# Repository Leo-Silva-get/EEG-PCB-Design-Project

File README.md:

# DIY 8-Channel EEG Acquisition System

### Custom ADS1299 + ESP32-S3 Hardware for Brain-Computer Interface Research

A custom four-layer, eight-channel EEG acquisition PCB designed in KiCad to explore neural signal acquisition and motor-imagery-based brain-computer interfaces.

## Project Overview

This project focuses on designing EEG acquisition hardware from the component level, rather than relying on a commercial EEG development board.

The system is designed around the Texas Instruments ADS1299 analog front end and an ESP32-S3 microcontroller.

**Hardware features:**
- Eight EEG acquisition channels using the ADS1299
- ESP32-S3 microcontroller with SPI communication
- Custom positive and negative analog power supplies
- Electrode input filtering and protection
- USB-C connectivity
- microSD hardware interface for future data recording
- LIS3DH accelerometer for movement measurements
- Four-layer PCB with dedicated internal ground planes

## Engineering Work

Designed the schematic and PCB in KiCad, including component selection, power distribution, signal routing, input filtering, decoupling, and manufacturing documentation.

The project includes Gerber files, an assembly BOM, component placement information, and design source files.

## Current Status

**PCB design completed; professional fabrication and assembly review in progress.**

Hardware bring-up, firmware development, signal characterization, and motor-imagery experiments are planned next.

This design has not yet been validated through physical testing or evaluated for human electrical safety.

## Research Objectives

1. Validate ADS1299 communication and register configuration.
2. Acquire and analyze low-noise EEG signals.
3. Implement real-time sampling and data streaming.
4. Develop signal-processing and classification methods for motor imagery.
5. Explore EEG-based control of computer applications.

## Tools and Technologies

KiCad, ADS1299, ESP32-S3, SPI, analog circuit design, PCB layout, embedded systems, and digital signal processing.

## Safety

This is an experimental research prototype, not a certified medical device. Human-connected use requires appropriate electrical-safety evaluation, including isolation and electrode fault-current assessment.

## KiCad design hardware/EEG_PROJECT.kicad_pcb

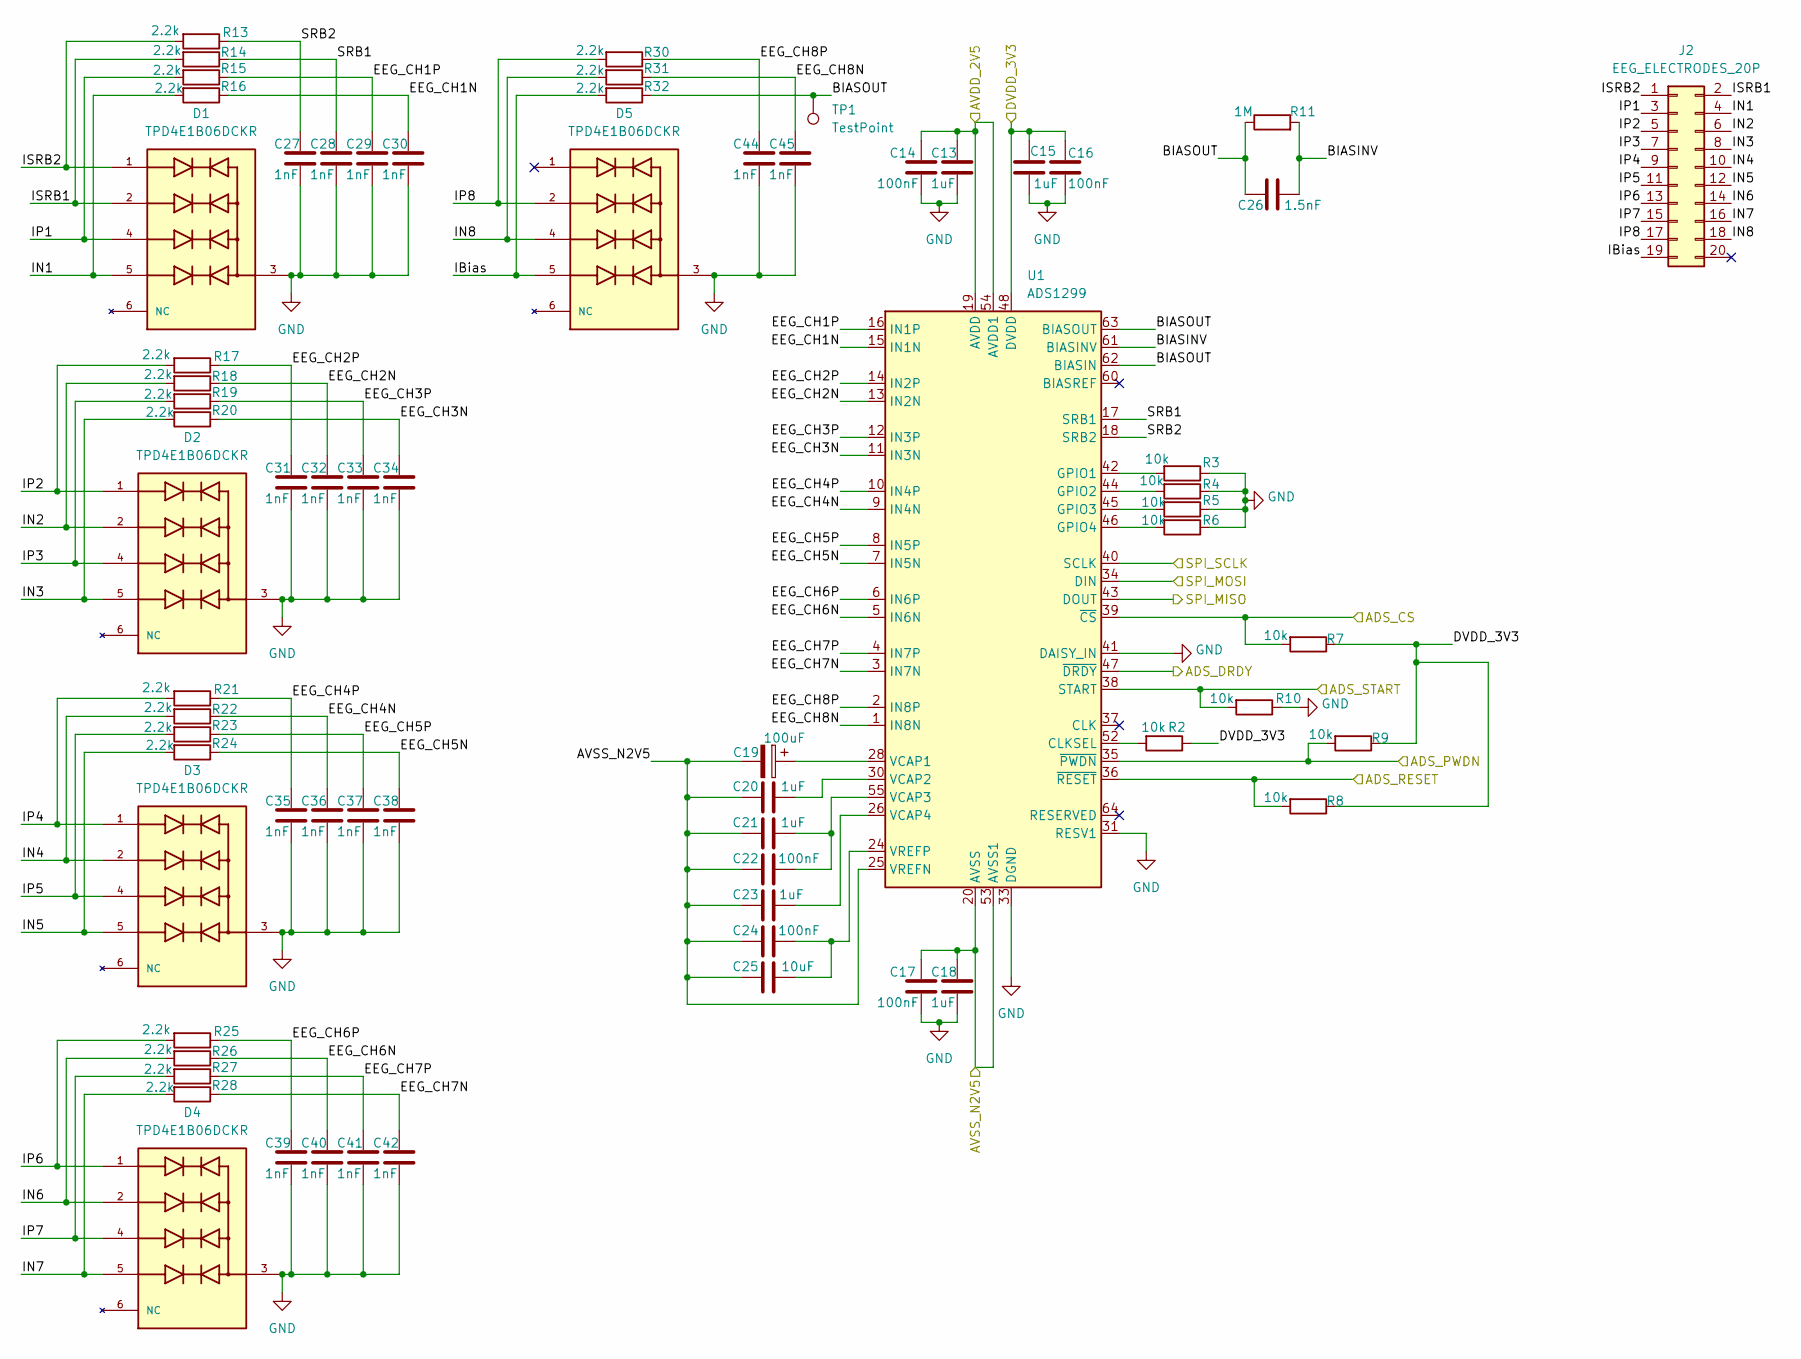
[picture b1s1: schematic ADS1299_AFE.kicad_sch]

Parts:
C13, C15, C18, C20, C21, C23: 1uF; C_0603_1608Metric; Tolerance 10%; Voltage rating 16V; MPN C0603C105K4RACTU
C14, C16, C17, C22, C24: 100nF; C_0603_1608Metric; Tolerance 10%; Voltage rating 100V; MPN GRM188R72A104KA35D
C19: 100uF; CP_EIA-3528-21_Kemet-B; Tolerance 20%; Voltage rating 10V; MPN T495B107M010ATE350
C25: 10uF; C_1206_3216Metric; Tolerance 10%; Voltage rating 16V; MPN GRM31CR71C106KAC7L
C26: 1.5nF; C_0603_1608Metric; Tolerance 5%; Voltage rating 50V; MPN GRM1885C1H152JA01D
C27, C28, C29, C30, C31, C32, C33, C34, C35, C36, C37, C38, C39, C40, C41, C42, C44, C45: 1nF; C_0603_1608Metric; Tolerance 5%; Voltage rating 50V; MPN GRM1885C1H102JA01D
D1, D2, D3, D4, D5: TPD4E1B06DCKR; TVS_TPD4E1B06DCKR; PARTREV C
J2: EEG_ELECTRODES_20P; PinHeader_2x10_P2.54mm_Vertical; MPN TSW-110-07-G-D
R2, R3, R4, R5, R6, R7, R8, R9, R10: 10k; R_0603_1608Metric; Power Rating 0.1 W; Tolerance ±1%; MPN RC0603FR-0710KL
R11: 1M; R_0603_1608Metric; Power Rating 0.1 W; Tolerance ±1%; MPN RC0603FR-071ML
R13, R14, R15, R16, R17, R18, R19, R20, R21, R22, R23, R24, R25, R26, R27, R28, R30, R31, R32: 2.2k; R_0603_1608Metric; Power Rating 0.1 W; Tolerance ±1%; MPN RC0603FR-072K2L
TP1: TestPoint; TestPoint_Pad_D1.5mm; MPN N/A
U1: ADS1299; TQFP-64_10x10mm_P0.5mm; MPN ADS1299IPAG

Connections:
/ADS1299_AFE/ADS_CS: R7.2, U1.39 (~CS); also elsewhere on the board
/ADS1299_AFE/ADS_DRDY: U1.47 (~DRDY); also elsewhere on the board
/ADS1299_AFE/ADS_PWDN: R9.2, U1.35 (~PWDN); also elsewhere on the board
/ADS1299_AFE/ADS_RESET: R8.2, U1.36 (~RESET); also elsewhere on the board
/ADS1299_AFE/ADS_START: R10.2, U1.38 (START); also elsewhere on the board
/ADS1299_AFE/AVDD_2V5: C13.1, C14.1, U1.19 (AVDD), U1.21 (AVDD), U1.22 (AVDD), U1.54 (AVDD1), U1.56 (AVDD), U1.59 (AVDD); also elsewhere on the board
/ADS1299_AFE/AVSS_N2V5: C17.1, C18.1, C19.2, C20.1, C21.1, C22.1, C23.1, C24.1, C25.1, U1.20 (AVSS), U1.23 (AVSS), U1.25 (VREFN), U1.32 (AVSS), U1.53 (AVSS1), U1.57 (AVSS), U1.58 (AVSS); also elsewhere on the board
/ADS1299_AFE/BIASINV: C26.2, R11.2, U1.61 (BIASINV)
/ADS1299_AFE/BIASOUT: C26.1, R11.1, R32.1, TP1.1 (1_1), U1.62 (BIASIN), U1.63 (BIASOUT)
/ADS1299_AFE/DVDD_3V3: C15.1, C16.1, R2.1, R7.1, R8.1, R9.1, U1.48 (DVDD), U1.50 (DVDD); also elsewhere on the board
/ADS1299_AFE/EEG_CH1N: C30.1, R16.1, U1.15 (IN1N)
/ADS1299_AFE/EEG_CH1P: C29.1, R15.1, U1.16 (IN1P)
/ADS1299_AFE/EEG_CH2N: C32.1, R18.1, U1.13 (IN2N)
/ADS1299_AFE/EEG_CH2P: C31.1, R17.1, U1.14 (IN2P)
/ADS1299_AFE/EEG_CH3N: C34.1, R20.1, U1.11 (IN3N)
/ADS1299_AFE/EEG_CH3P: C33.1, R19.1, U1.12 (IN3P)
/ADS1299_AFE/EEG_CH4N: C36.1, R22.1, U1.9 (IN4N)
/ADS1299_AFE/EEG_CH4P: C35.1, R21.1, U1.10 (IN4P)
/ADS1299_AFE/EEG_CH5N: C38.1, R24.1, U1.7 (IN5N)
/ADS1299_AFE/EEG_CH5P: C37.1, R23.1, U1.8 (IN5P)
/ADS1299_AFE/EEG_CH6N: C40.1, R26.1, U1.5 (IN6N)
/ADS1299_AFE/EEG_CH6P: C39.1, R25.1, U1.6 (IN6P)
/ADS1299_AFE/EEG_CH7N: C42.1, R28.1, U1.3 (IN7N)
/ADS1299_AFE/EEG_CH7P: C41.1, R27.1, U1.4 (IN7P)
/ADS1299_AFE/EEG_CH8N: C45.1, R31.1, U1.1 (IN8N)
/ADS1299_AFE/EEG_CH8P: C44.1, R30.1, U1.2 (IN8P)
/ADS1299_AFE/IBias: D5.5, J2.19, R32.2
/ADS1299_AFE/IN1: D1.5, J2.4, R16.2
/ADS1299_AFE/IN2: D2.2, J2.6, R18.2
/ADS1299_AFE/IN3: D2.5, J2.8, R20.2
/ADS1299_AFE/IN4: D3.2, J2.10, R22.2
/ADS1299_AFE/IN5: D3.5, J2.12, R24.2
/ADS1299_AFE/IN6: D4.2, J2.14, R26.2
/ADS1299_AFE/IN7: D4.5, J2.16, R28.2
/ADS1299_AFE/IN8: D5.4, J2.18, R31.2
/ADS1299_AFE/IP1: D1.4, J2.3, R15.2
/ADS1299_AFE/IP2: D2.1, J2.5, R17.2
/ADS1299_AFE/IP3: D2.4, J2.7, R19.2
/ADS1299_AFE/IP4: D3.1, J2.9, R21.2
/ADS1299_AFE/IP5: D3.4, J2.11, R23.2
/ADS1299_AFE/IP6: D4.1, J2.13, R25.2
/ADS1299_AFE/IP7: D4.4, J2.15, R27.2
/ADS1299_AFE/IP8: D5.2, J2.17, R30.2
/ADS1299_AFE/ISRB1: D1.2, J2.2, R14.2
/ADS1299_AFE/ISRB2: D1.1, J2.1, R13.2
/ADS1299_AFE/SPI_MISO: U1.43 (DOUT); also elsewhere on the board
/ADS1299_AFE/SPI_MOSI: U1.34 (DIN); also elsewhere on the board
/ADS1299_AFE/SPI_SCLK: U1.40 (SCLK); also elsewhere on the board
/ADS1299_AFE/SRB1: C28.1, R14.1, U1.17 (SRB1)
/ADS1299_AFE/SRB2: C27.1, R13.1, U1.18 (SRB2)
GND: C13.2, C14.2, C15.2, C16.2, C17.2, C18.2, C27.2, C28.2, C29.2, C30.2, C31.2, C32.2, C33.2, C34.2, C35.2, C36.2, C37.2, C38.2, C39.2, C40.2, C41.2, C42.2, C44.2, C45.2, D1.3, D2.3, D3.3, D4.3, D5.3, R3.1, R4.1, R5.1, R6.1, R10.1, U1.31 (RESV1), U1.33 (DGND), U1.41 (DAISY_IN), U1.49 (DGND), U1.51 (DGND); also elsewhere on the board
unnamed: R2.2, U1.52 (CLKSEL)
unnamed: R3.2, U1.42 (GPIO1)
unnamed: R4.2, U1.44 (GPIO2)
unnamed: R5.2, U1.45 (GPIO3)
unnamed: R6.2, U1.46 (GPIO4)
unnamed: C19.1, U1.28 (VCAP1)
unnamed: C20.2, U1.30 (VCAP2)
unnamed: C21.2, C22.2, U1.55 (VCAP3)
unnamed: C23.2, U1.26 (VCAP4)
unnamed: C24.2, C25.2, U1.24 (VREFP)

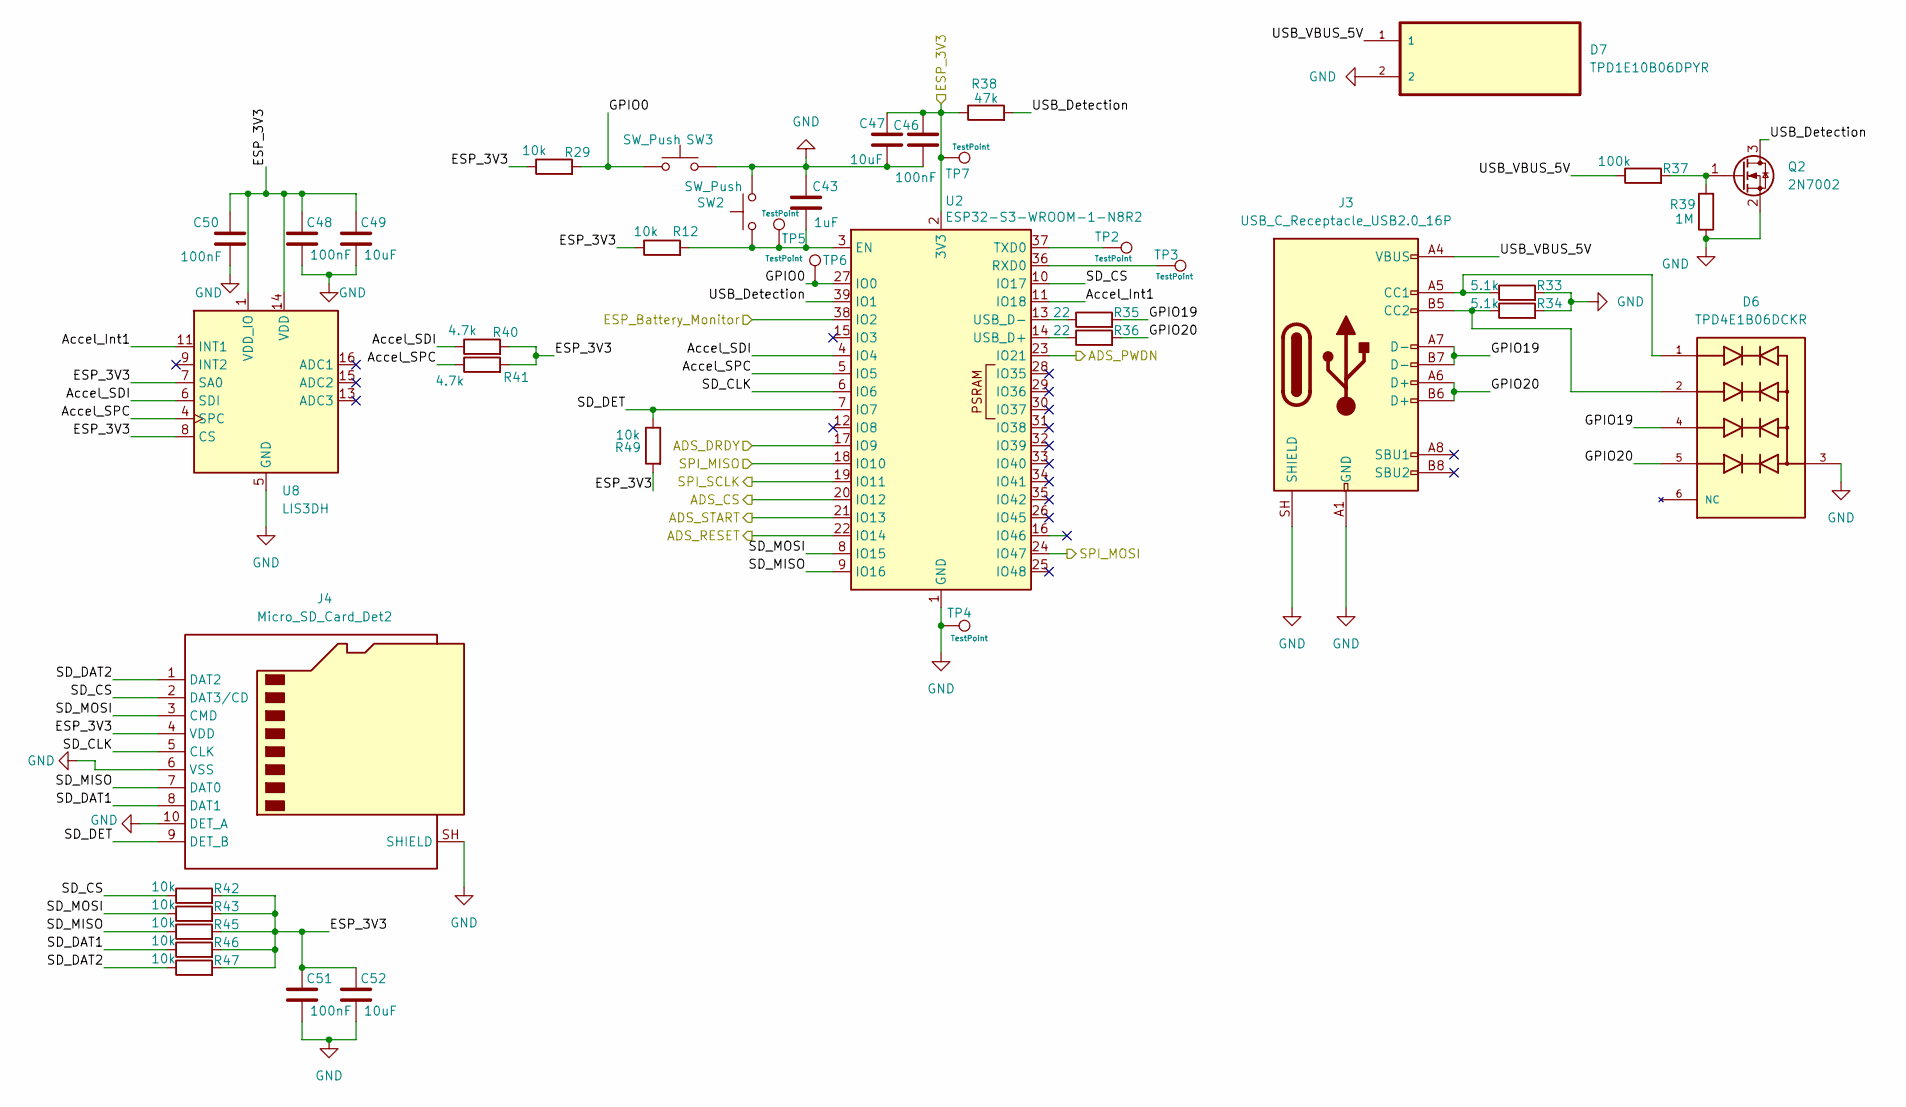
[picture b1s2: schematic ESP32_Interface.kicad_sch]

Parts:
C43: 1uF; C_0603_1608Metric; Tolerance 10%; Voltage rating 16V; MPN C0603C105K4RACTU
C46, C48, C50, C51: 100nF; C_0603_1608Metric; Tolerance 10%; Voltage rating 100V; MPN GRM188R72A104KA35D
C47, C49, C52: 10uF; C_1206_3216Metric; Tolerance 10%; Voltage rating 16V; MPN GRM31CR71C106KAC7L
D6: TPD4E1B06DCKR; TVS_TPD4E1B06DCKR; PARTREV C
D7: TPD1E10B06DPYR; DIO_TPD1E10B06DPYR; MPN TPD1E10B06DPYR; DigiKey_Part_Number 296-41842-1-ND
J3: USB_C_Receptacle_USB2.0_16P; USB_C_Receptacle_GCT_USB4085; MPN USB4085-GF-A
J4: Micro_SD_Card_Det2; microSD_HC_Molex_104031-0811; MPN 104031-0811
Q2: 2N7002; SOT-23; MPN 2N7002LT1G
R12, R29, R42, R43, R45, R46, R47, R49: 10k; R_0603_1608Metric; Power Rating 0.1 W; Tolerance ±1%; MPN RC0603FR-0710KL
R33, R34: 5.1k; R_0603_1608Metric; Power Rating 0.1 W; Tolerance ±1%; MPN RC0603FR-075K1L
R35, R36: 22; R_0603_1608Metric; Power Rating 0.1 W; Tolerance ±1%; MPN RC0603FR-0722RL
R37: 100k; R_0603_1608Metric; Power Rating 0.1 W; Tolerance ±1%; MPN RC0603FR-07100KL
R38: 47k; R_0603_1608Metric; Power Rating 0.1 W; Tolerance ±1%; MPN RC0603FR-0747KL
R39: 1M; R_0603_1608Metric; Power Rating 0.1 W; Tolerance ±1%; MPN RC0603FR-071ML
R40, R41: 4.7k; R_0603_1608Metric; Power Rating 0.1 W; Tolerance ±1%; MPN RC0603FR-074K7L
SW2, SW3: SW_Push; SW_SPST_B3U-1000P; MPN B3U-1000P
TP2, TP3, TP4, TP5, TP6, TP7: TestPoint; TestPoint_Pad_D1.5mm; MPN N/A
U2: ESP32-S3-WROOM-1-N8R2; ESP32-S3-WROOM-1; MPN ESP32-S3-WROOM-1-N8R2
U8: LIS3DH; LGA-16_3x3mm_P0.5mm_LayoutBorder3x5y; MPN LIS3DHTR

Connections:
/ADS1299_AFE/ADS_CS: U2.20 (IO12); also elsewhere on the board
/ADS1299_AFE/ADS_DRDY: U2.17 (IO9); also elsewhere on the board
/ADS1299_AFE/ADS_PWDN: U2.23 (IO21); also elsewhere on the board
/ADS1299_AFE/ADS_RESET: U2.22 (IO14); also elsewhere on the board
/ADS1299_AFE/ADS_START: U2.21 (IO13); also elsewhere on the board
/ADS1299_AFE/SPI_MISO: U2.18 (IO10); also elsewhere on the board
/ADS1299_AFE/SPI_MOSI: U2.24 (IO47); also elsewhere on the board
/ADS1299_AFE/SPI_SCLK: U2.19 (IO11); also elsewhere on the board
/ESP32_Interface/Accel_Int1: U2.11 (IO18), U8.11 (INT1)
/ESP32_Interface/Accel_SDI: R40.1, U2.4 (IO4), U8.6 (SDI)
/ESP32_Interface/Accel_SPC: R41.1, U2.5 (IO5), U8.4 (SPC)
/ESP32_Interface/ESP_3V3: C46.1, C47.1, C48.1, C49.1, C50.1, C51.1, C52.1, J4.4 (VDD), R12.1, R29.1, R38.1, R40.2, R41.2, R42.2, R43.2, R45.2, R46.2, R47.2, R49.2, TP7.1 (1_1), U2.2 (3V3), U8.1 (VDD_IO), U8.7 (SA0), U8.8 (CS), U8.14 (VDD); also elsewhere on the board
/ESP32_Interface/ESP_Battery_Monitor: U2.38 (IO2); also elsewhere on the board
/ESP32_Interface/GPIO0: R29.2, SW3.1, TP6.1 (1_1), U2.27 (IO0)
/ESP32_Interface/GPIO19: D6.4, J3.A7 (D-), J3.B7 (D-), R35.2
/ESP32_Interface/GPIO20: D6.5, J3.A6 (D+), J3.B6 (D+), R36.2
/ESP32_Interface/SD_CLK: J4.5 (CLK), U2.6 (IO6)
/ESP32_Interface/SD_CS: J4.2 (DAT3/CD), R42.1, U2.10 (IO17)
/ESP32_Interface/SD_DAT1: J4.8 (DAT1), R46.1
/ESP32_Interface/SD_DAT2: J4.1 (DAT2), R47.1
/ESP32_Interface/SD_DET: J4.9 (DET_B), R49.1, U2.7 (IO7)
/ESP32_Interface/SD_MISO: J4.7 (DAT0), R45.1, U2.9 (IO16)
/ESP32_Interface/SD_MOSI: J4.3 (CMD), R43.1, U2.8 (IO15)
/ESP32_Interface/USB_Detection: Q2.3 (D), R38.2, U2.39 (IO1)
/ESP32_Interface/USB_VBUS_5V: D7.1, J3.A4 (VBUS), J3.A9 (VBUS), J3.B4 (VBUS), J3.B9 (VBUS), R37.1
GND: C43.1, C46.2, C47.2, C48.2, C49.2, C50.2, C51.2, C52.2, D6.3, D7.2, J3.A1 (GND), J3.A12 (GND), J3.B1 (GND), J3.B12 (GND), J3.SH (SHIELD), J4.6 (VSS), J4.10 (DET_A), J4.SH (SHIELD), Q2.2 (S), R33.2, R34.2, R39.1, SW2.2, SW3.2, TP4.1 (1_1), U2.1 (GND), U2.40 (GND), U2.41 (GND), U8.5 (GND), U8.10 (GND), U8.12 (GND); also elsewhere on the board
unnamed: D6.1, J3.A5 (CC1), R33.1
unnamed: D6.2, J3.B5 (CC2), R34.1
unnamed: Q2.1 (G), R37.2, R39.2
unnamed: C43.2, R12.2, SW2.1, TP5.1 (1_1), U2.3 (EN)
unnamed: TP3.1 (1_1), U2.36 (RXD0)
unnamed: TP2.1 (1_1), U2.37 (TXD0)
unnamed: R36.1, U2.14 (USB_D+)
unnamed: R35.1, U2.13 (USB_D-)

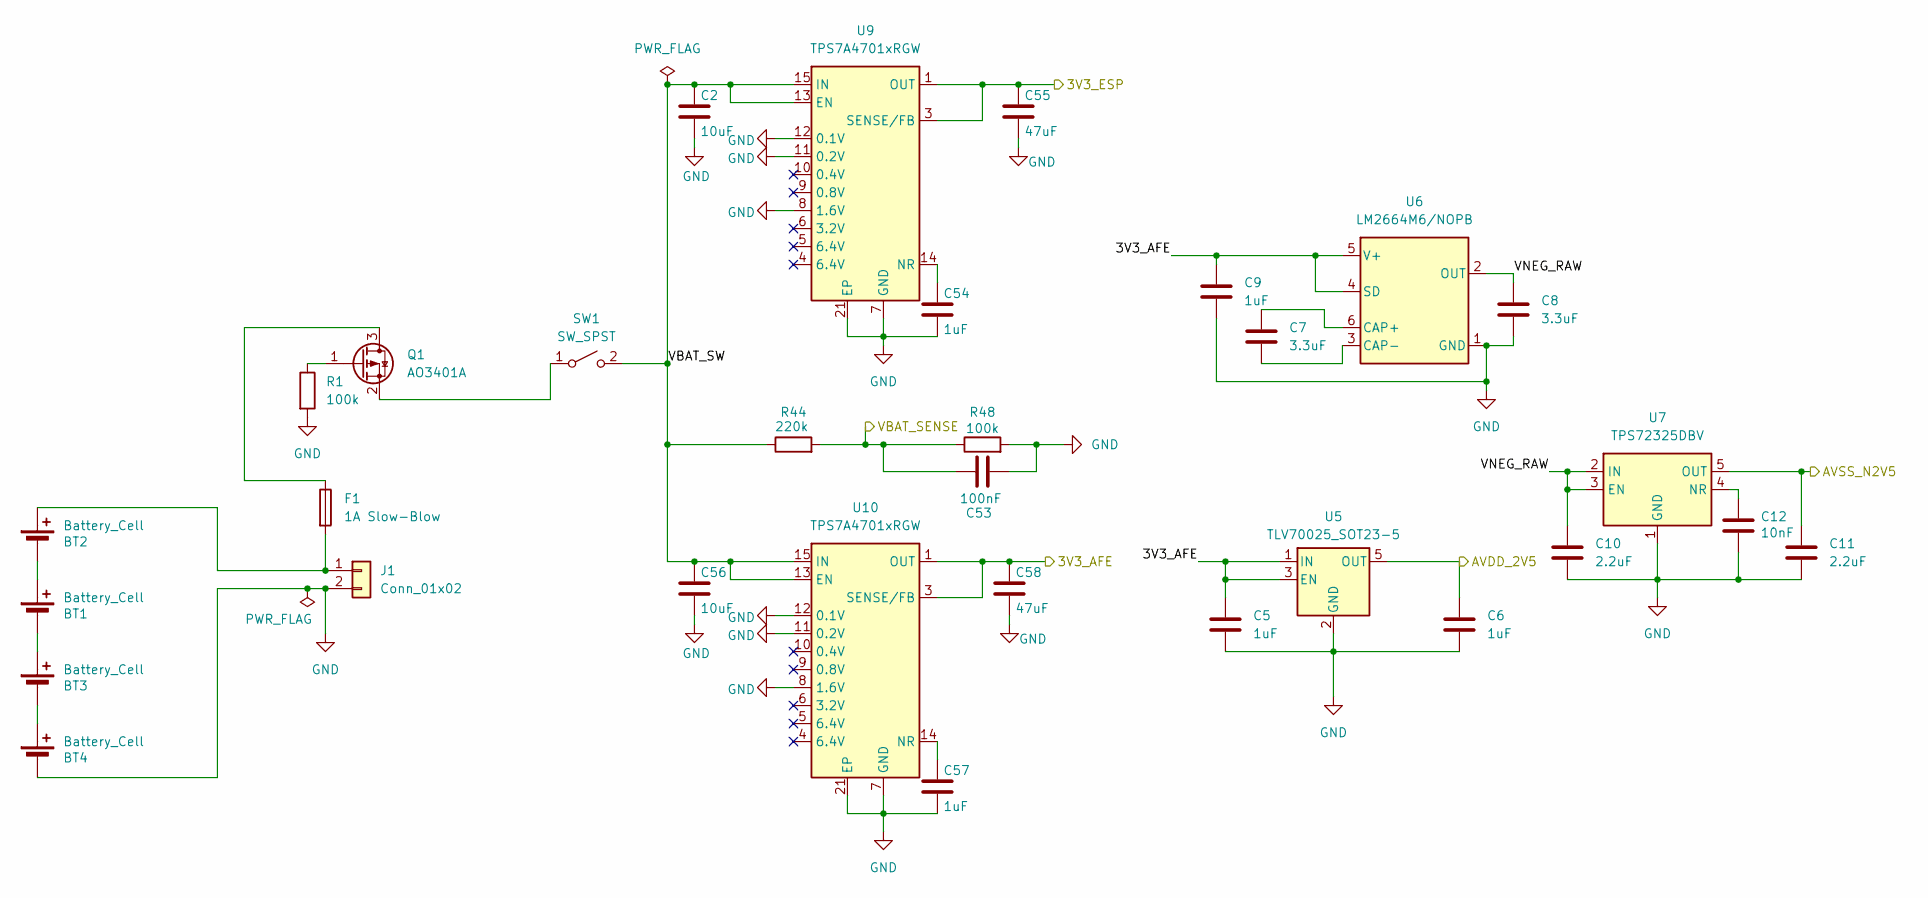
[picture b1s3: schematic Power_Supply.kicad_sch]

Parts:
BT1, BT2, BT3, BT4: Battery_Cell
C2, C56: 10uF; C_1206_3216Metric; Tolerance 10%; Voltage rating 16V; MPN GRM31CR71C106KAC7L
C5, C6, C9, C54, C57: 1uF; C_0805_2012Metric; Tolerance 10%; Voltage rating 25V; MPN C2012X7R1E105K125AB
C7, C8: 3.3uF; C_1206_3216Metric; Tolerance 10%; Voltage rating 25V; MPN C1206C335K3RACTU
C10, C11: 2.2uF; C_0805_2012Metric; Tolerance 10%; Voltage rating 50V; MPN C2012X7R1H225K125AC
C12: 10nF; C_0603_1608Metric; Tolerance 10%; Voltage rating 100V; MPN GRM188R72A103KA01D
C53: 100nF; C_0603_1608Metric; Tolerance 10%; Voltage rating 100V; MPN GRM188R72A104KA35D
C55, C58: 47uF; C_1210_3225Metric; Tolerance 10%; Voltage rating 16V; MPN CL32A476KOJNNNE
F1: 1A Slow-Blow; SF-1206S100-2; MPN SF-1206S100-2
J1: Conn_01x02; JST_PH_B2B-PH-K_1x02_P2.00mm_Vertical; MPN B2B-PH-K-S(LF)(SN)
Q1: AO3401A; SOT-23; MPN AO3401A
R1, R48: 100k; R_0603_1608Metric; Power Rating 0.1 W; Tolerance ±1%; MPN RC0603FR-07100KL
R44: 220k; R_0603_1608Metric; Power Rating 0.1 W; Tolerance ±1%; MPN RC0603FR-07220KL
SW1: SW_SPST; SW_CW_GPTS203211B; MPN GPTS203211B
U5: TLV70025_SOT23-5; SOT-23-5; MPN TLV70025DDCR
U6: LM2664M6/NOPB; SOT-23-6; MPN LM2664M6/NOPB
U7: TPS72325DBV; SOT-23-5; MPN TPS72325DBVR
U9, U10: TPS7A4701xRGW; Texas_RGW0020A_VQFN-20-1EP_5x5mm_P0.65mm_EP3.15x3.15mm_Ther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; MPN TPS7A4701RGWR

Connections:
/ADS1299_AFE/AVDD_2V5: C6.1, U5.5 (OUT); also elsewhere on the board
/ADS1299_AFE/AVSS_N2V5: C11.1, U7.5 (OUT); also elsewhere on the board
/ADS1299_AFE/DVDD_3V3: C5.1, C9.1, C58.1, U5.1 (IN), U5.3 (EN), U6.4 (SD), U6.5 (V+), U10.1 (OUT), U10.3 (SENSE/FB), U10.20 (OUT); also elsewhere on the board
/ESP32_Interface/ESP_3V3: C55.1, U9.1 (OUT), U9.3 (SENSE/FB), U9.20 (OUT); also elsewhere on the board
/ESP32_Interface/ESP_Battery_Monitor: C53.1, R44.2, R48.1; also elsewhere on the board
/Power_Supply/VBAT_SW: C2.1, C56.1, R44.1, SW1.2 (B), U9.13 (EN), U9.15 (IN), U9.16 (IN), U10.13 (EN), U10.15 (IN), U10.16 (IN)
/Power_Supply/VNEG_RAW: C8.1, C10.1, U6.2 (OUT), U7.2 (IN), U7.3 (EN)
GND: BT4.2 (-), C2.2, C5.2, C6.2, C8.2, C9.2, C10.2, C11.2, C12.2, C53.2, C54.2, C55.2, C56.2, C57.2, C58.2, J1.2, R1.2, R48.2, U5.2 (GND), U6.1 (GND), U7.1 (GND), U9.7 (GND), U9.8 (1.6V), U9.11 (0.2V), U9.12 (0.1V), U9.21 (EP), U10.7 (GND), U10.8 (1.6V), U10.11 (0.2V), U10.12 (0.1V), U10.21 (EP); also elsewhere on the board
unnamed: BT1.1 (+), BT2.2 (-)
unnamed: BT1.2 (-), BT3.1 (+)
unnamed: BT3.2 (-), BT4.1 (+)
unnamed: BT2.1 (+), F1.2, J1.1
unnamed: F1.1, Q1.3 (D)
unnamed: Q1.1 (G), R1.1
unnamed: Q1.2 (S), SW1.1 (A)
unnamed: C7.1, U6.6 (CAP+)
unnamed: C7.2, U6.3 (CAP-)
unnamed: C12.1, U7.4 (NR)
unnamed: C54.1, U9.14 (NR)
unnamed: C57.1, U10.14 (NR)

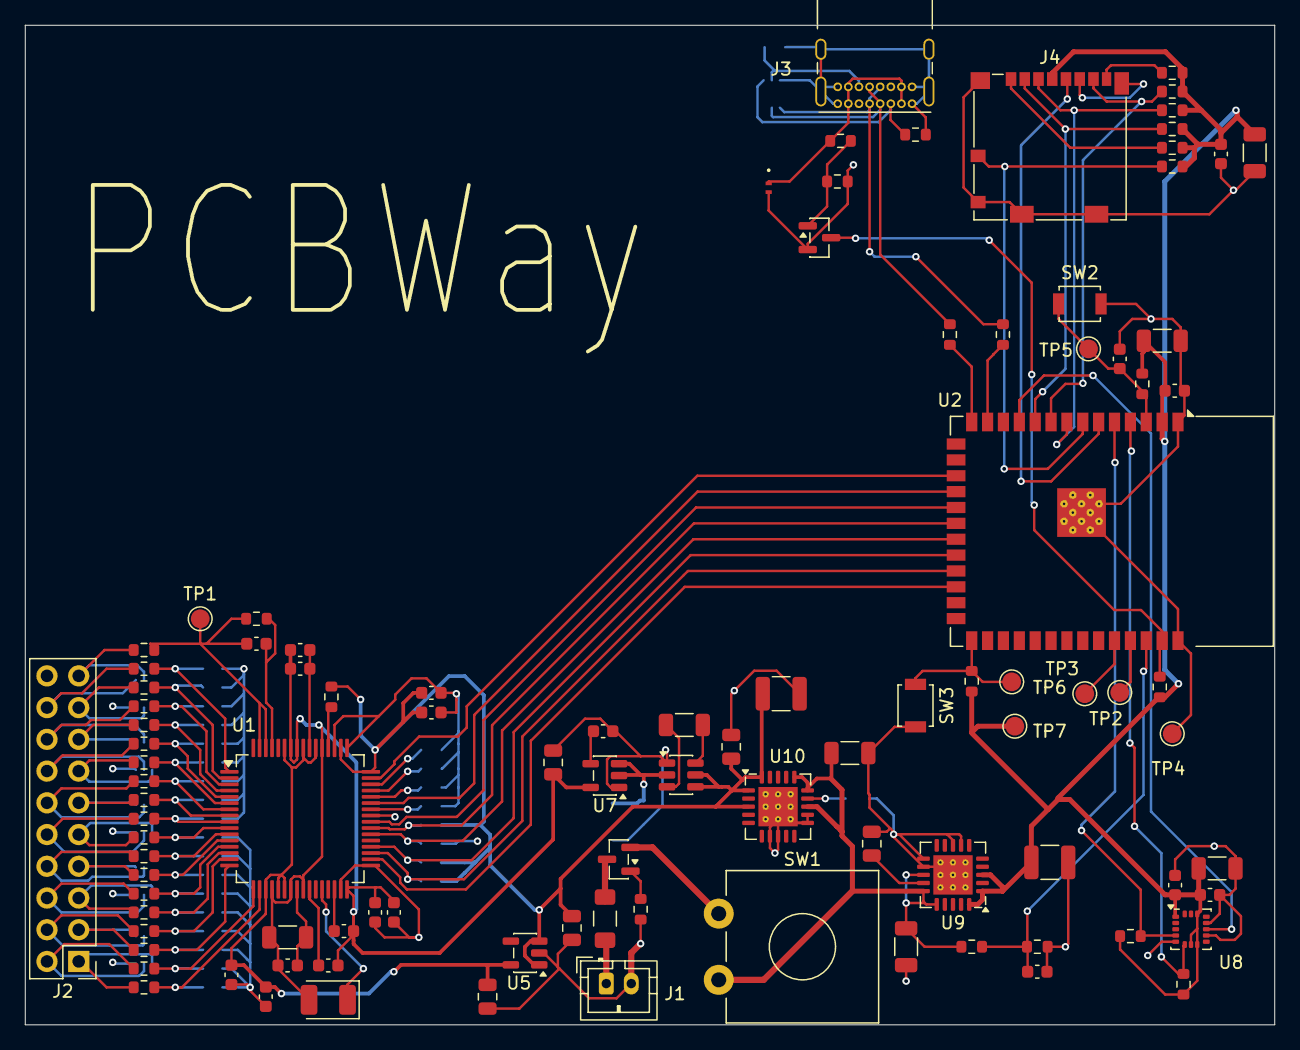
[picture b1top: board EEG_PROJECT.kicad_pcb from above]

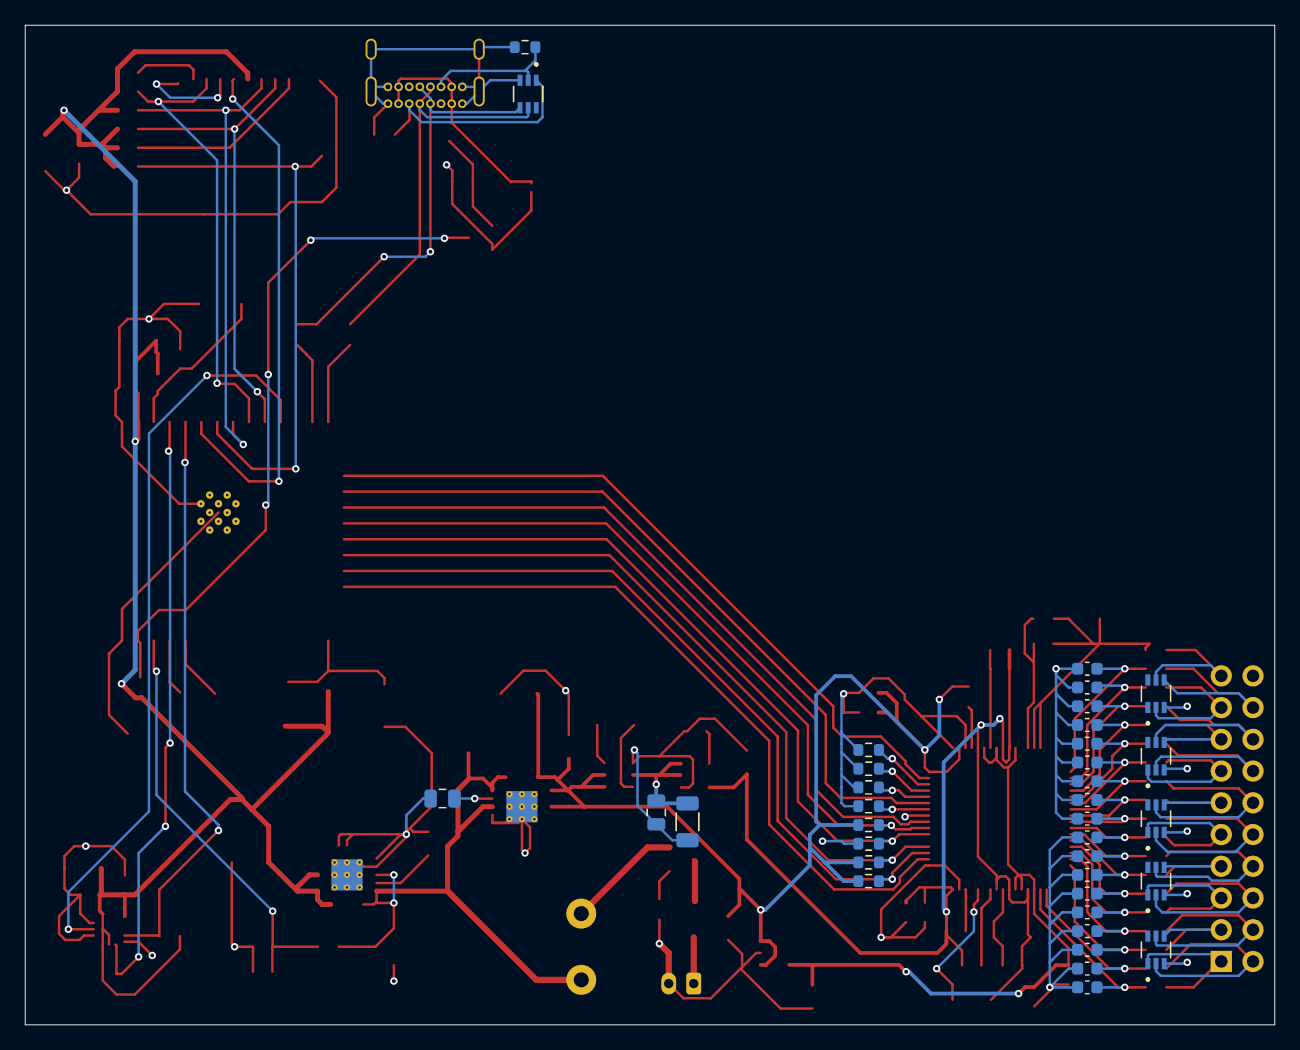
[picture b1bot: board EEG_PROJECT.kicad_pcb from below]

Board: 4 copper layers, 100.0 x 80.0 mm, 136 parts (36 on the bottom side), 97 nets.

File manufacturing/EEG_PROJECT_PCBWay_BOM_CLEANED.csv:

Reference,Qty,Value,Manufacturer,MPN,Footprint,Assembly Type,Datasheet,Voltage Rating,Tolerance,Dielectric,Power Rating
"C2, C25, C47, C49, C52, C56",6,10uF,Murata,GRM31CR71C106KAC7L,Capacitor_SMD:C_1206_3216Metric,Surface mount,https://www.digikey.com/en/products/detail/murata-electronic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,16V,10%,X7R ceramic,
"C5, C6, C9, C54, C57",5,1uF,TDK,C2012X7R1E105K125AB,Capacitor_SMD:C_0805_2012Metric,Surface mount,https://www.digikey.com/en/products/detail/tdk-corporation/C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,25V,10%,X7R ceramic,
"C7, C8",2,3.3uF,KEMET,C1206C335K3RACTU,Capacitor_SMD:C_1206_3216Metric,Surface mount,https://www.digikey.com/en/products/detail/kemet/C1206C335K3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,25V,10%,X7R ceramic,
"C10, C11",2,2.2uF,TDK,C2012X7R1H225K125AC,Capacitor_SMD:C_0805_2012Metric,Surface mount,https://www.digikey.com/en/products/detail/tdk/C2012X7R1H225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,50V,10%,X7R ceramic,
C12,1,10nF,Murata,GRM188R72A103KA01D,Capacitor_SMD:C_0603_1608Metric,Surface mount,https://www.digikey.com/en/products/detail/murata-electronic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,100V,10%,X7R ceramic,
"C13, C15, C18, C20, C21, C23, C43",7,1uF,KEMET,C0603C105K4RACTU,Capacitor_SMD:C_0603_1608Metric,Surface mount,https://www.digikey.com/en/products/detail/kemet/C0603C105K4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,16V,10%,X7R ceramic,
"C14, C16, C17, C22, C24, C46, C48, C50, C51, C53",10,100nF,Murata,GRM188R72A104KA35D,Capacitor_SMD:C_0603_1608Metric,Surface mount,https://www.digikey.com/en/products/detail/murata-electronic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,100V,10%,X7R ceramic,
C19,1,100uF,KEMET,T495B107M010ATE350,Capacitor_Tantalum_SMD:CP_EIA-3528-21_Kemet-B,Surface mount,https://www.digikey.com/en/products/detail/kemet/T495B107M01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,10V,20%,Molded tantalum; ESR 0.35 Ω @100 kHz,
C26,1,1.5nF,Murata,GRM1885C1H152JA01D,Capacitor_SMD:C_0603_1608Metric,Surface mount,https://www.digikey.com/en/products/detail/murata-electronic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,50V,5%,C0G / NP0 ceramic,
"C27, C28, C29, C30, C31, C32, C33, C34, C35, C36, C37, C38, C39, C40, C41, C42, C44, C45",18,1nF,Murata,GRM1885C1H102JA01D,Capacitor_SMD:C_0603_1608Metric,Surface mount,https://www.digikey.com/en/products/detail/murata-electronic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,50V,5%,C0G / NP0 ceramic,
"C55, C58",2,47uF,Samsung Electro-Mechanics,CL32A476KOJNNNE,Capacitor_SMD:C_1210_3225Metric,Surface mount,https://www.digikey.com/en/products/detail/samsung-electro-m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,16V,10%,X5R ceramic,
"D1, D2, D3, D4, D5, D6",6,TPD4E1B06DCKR,Texas Instruments,TPD4E1B06DCKR,Library:TVS_TPD4E1B06DCKR,Surface mount,https://www.ti.com/product/TPD4E1B06,,,ESD / TVS,
D7,1,TPD1E10B06DPYR,Texas Instruments,TPD1E10B06DPYR,Library:DIO_TPD1E10B06DPYR,Surface mount,https://www.ti.com/product/TPD1E10B06,,,ESD / TVS,
F1,1,1A Slow-Blow,Bourns,SF-1206S100-2,Library:SF-1206S100-2,Surface mount,https://www.bourns.com/docs/product-datasheets/sf-1206s.pdf,,,"Slow-blow, non-resettable fuse",
J1,1,Conn_01x02,JST,B2B-PH-K-S(LF)(SN),Connector_JST:JST_PH_B2B-PH-K_1x02_P2.00mm_Vertical,Through-hole,https://www.digikey.com/en/products/detail/jst-sales-america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,,,,
J2,1,EEG_ELECTRODES_20P,Samtec,TSW-110-07-G-D,Connector_PinHeader_2.54mm:PinHeader_2x10_P2.54mm_Vertical,Through-hole,https://www.digikey.com/en/products/detail/samtec-inc/TSW-11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,,,,
J3,1,USB_C_Receptacle_USB2.0_16P,GCT,USB4085-GF-A,Connector_USB:USB_C_Receptacle_GCT_USB4085,Through-hole,https://www.digikey.com/en/products/detail/gct/USB4085-GF-A/9859662,,,,
J4,1,Micro_SD_Card_Det2,Molex,104031-0811,Connector_Card:microSD_HC_Molex_104031-0811,Surface mount,https://www.digikey.com/en/products/detail/molex/1040310811/2370379,,,,
Q1,1,AO3401A,Alpha & Omega Semiconductor,AO3401A,Package_TO_SOT_SMD:SOT-23,Surface mount,https://www.digikey.com/en/products/detail/alpha-omega-semic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,,,SOT-23 MOSFET,
Q2,1,2N7002,Onsemi,2N7002LT1G,Package_TO_SOT_SMD:SOT-23,Surface mount,https://www.digikey.com/en/products/detail/onsemi/2N7002LT1G/917791,,,SOT-23 MOSFET,
"R1, R37, R48",3,100k,YAGEO,RC0603FR-07100KL,Resistor_SMD:R_0603_1608Metric,Surface mount,https://www.digikey.com/en/products/detail/yageo/RC0603FR-07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,Max working voltage per YAGEO RC datasheet,±1%,Thick-film chip resistor,0.1 W
"R2, R3, R4, R5, R6, R7, R8, R9, R10, R12, R29, R42, R43, R45, R46, R47, R49",17,10k,YAGEO,RC0603FR-0710KL,Resistor_SMD:R_0603_1608Metric,Surface mount,https://www.digikey.com/en/products/detail/yageo/RC0603FR-07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,Max working voltage per YAGEO RC datasheet,±1%,Thick-film chip resistor,0.1 W
"R11, R39",2,1M,YAGEO,RC0603FR-071ML,Resistor_SMD:R_0603_1608Metric,Surface mount,https://www.digikey.com/en/products/detail/yageo/RC0603FR-07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,Max working voltage per YAGEO RC datasheet,±1%,Thick-film chip resistor,0.1 W
"R13, R14, R15, R16, R17, R18, R19, R20, R21, R22, R23, R24, R25, R26, R27, R28, R30, R31, R32",19,2.2k,YAGEO,RC0603FR-072K2L,Resistor_SMD:R_0603_1608Metric,Surface mount,https://www.digikey.com/en/products/detail/yageo/RC0603FR-07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,Max working voltage per YAGEO RC datasheet,±1%,Thick-film chip resistor,0.1 W
"R33, R34",2,5.1k,YAGEO,RC0603FR-075K1L,Resistor_SMD:R_0603_1608Metric,Surface mount,https://www.digikey.com/en/products/detail/yageo/RC0603FR-07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,Max working voltage per YAGEO RC datasheet,±1%,Thick-film chip resistor,0.1 W
"R35, R36",2,22,YAGEO,RC0603FR-0722RL,Resistor_SMD:R_0603_1608Metric,Surface mount,https://www.digikey.com/en/products/detail/yageo/RC0603FR-07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,Max working voltage per YAGEO RC datasheet,±1%,Thick-film chip resistor,0.1 W
R38,1,47k,YAGEO,RC0603FR-0747KL,Resistor_SMD:R_0603_1608Metric,Surface mount,https://www.digikey.com/en/products/detail/yageo/RC0603FR-07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,Max working voltage per YAGEO RC datasheet,±1%,Thick-film chip resistor,0.1 W
"R40, R41",2,4.7k,YAGEO,RC0603FR-074K7L,Resistor_SMD:R_0603_1608Metric,Surface mount,https://www.digikey.com/en/products/detail/yageo/RC0603FR-07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,Max working voltage per YAGEO RC datasheet,±1%,Thick-film chip resistor,0.1 W
R44,1,220k,YAGEO,RC0603FR-07220KL,Resistor_SMD:R_0603_1608Metric,Surface mount,https://www.digikey.com/en/products/detail/yageo/RC0603FR-07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,Max working voltage per YAGEO RC datasheet,±1%,Thick-film chip resistor,0.1 W
SW1,1,SW_SPST,CW Industries,GPTS203211B,Button_Switch_THT:SW_CW_GPTS203211B,Through-hole,https://www.digikey.com/en/products/detail/cw-industries/GPT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,,,Electromechanical switch,
"SW2, SW3",2,SW_Push,Aratas (formerly Omron Components),B3U-1000P,Button_Switch_SMD:SW_SPST_B3U-1000P,Surface mount,https://www.digikey.com/en/products/detail/omron-electronics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,,,Electromechanical switch,
U1,1,ADS1299,Texas Instruments,ADS1299IPAG,Package_QFP:TQFP-64_10x10mm_P0.5mm,Surface mount,https://www.ti.com/lit/ds/symlink/ads1299.pdf,,,,
U2,1,ESP32-S3-WROOM-1-N8R2,Espressif,ESP32-S3-WROOM-1-N8R2,RF_Module:ESP32-S3-WROOM-1,Surface mount,https://www.espressif.com/sites/default/files/documentation/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,,,,
U5,1,TLV70025_SOT23-5,Texas Instruments,TLV70025DDCR,Package_TO_SOT_SMD:SOT-23-5,Surface mount,https://www.digikey.com/en/products/detail/texas-instruments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,,,,
U6,1,LM2664M6/NOPB,Texas Instruments,LM2664M6/NOPB,Package_TO_SOT_SMD:SOT-23-6,Surface mount,https://www.ti.com/lit/ds/symlink/lm2664.pdf,,,,
U7,1,TPS72325DBV,Texas Instruments,TPS72325DBVR,Package_TO_SOT_SMD:SOT-23-5,Surface mount,https://www.ti.com/lit/ds/symlink/tps723.pdf,,,,
U8,1,LIS3DH,STMicroelectronics,LIS3DHTR,Package_LGA:LGA-16_3x3mm_P0.5mm_LayoutBorder3x5y,Surface mount,https://www.digikey.com/en/products/detail/stmicroelectronic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,,,,
"U9, U10",2,TPS7A4701xRGW,Texas Instruments,TPS7A4701RGWR,Package_DFN_QFN:Texas_RGW0020A_VQFN-20-1EP_5x5mm_P0.65mm_EP3.15x3.15mm_ThermalVias,Surface mount,https://www.ti.com/product/TPS7A47/part-details/TPS7A4701RGWR,,,,
